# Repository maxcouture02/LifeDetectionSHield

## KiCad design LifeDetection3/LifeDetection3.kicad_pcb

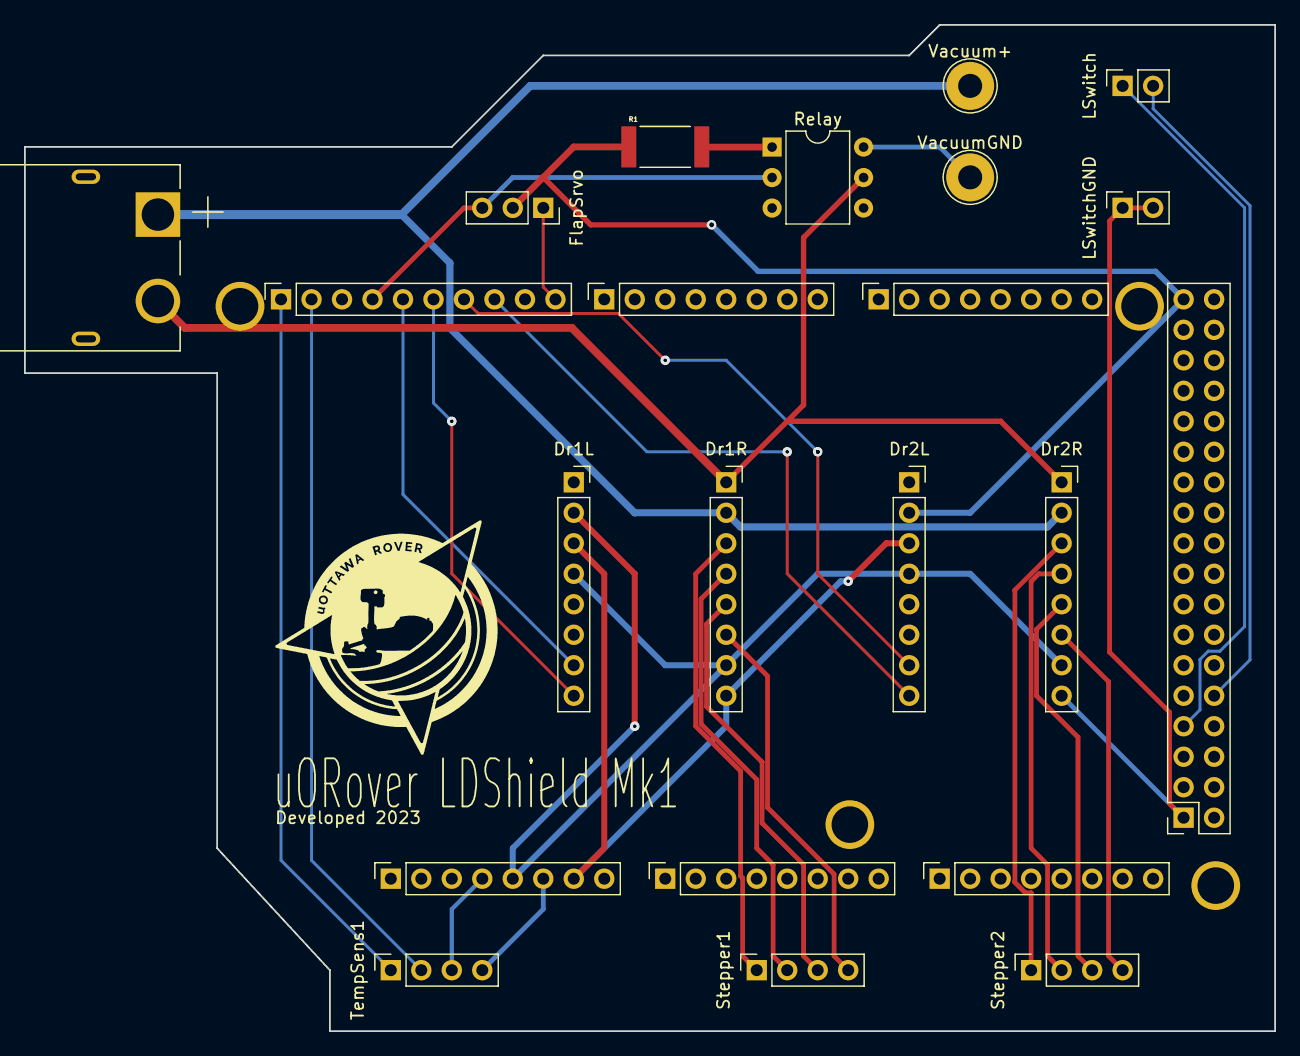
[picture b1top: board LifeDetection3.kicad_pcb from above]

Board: 2 copper layers, 104.1 x 83.8 mm, 22 parts (0 on the bottom side), 24 nets.

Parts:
Dr1L, Dr1R, Dr2L, Dr2R: Conn_01x08; PinSocket_1x08_P2.54mm_Vertical
FlapSrvo: Conn_01x03; PinSocket_1x03_P2.54mm_Vertical
J1: Power; PinSocket_1x08_P2.54mm_Vertical
J2: PWM; PinSocket_1x10_P2.54mm_Vertical
J3, J5: Analog; PinSocket_1x08_P2.54mm_Vertical
J4: PWM; PinSocket_1x08_P2.54mm_Vertical
J6: Communication; PinSocket_1x08_P2.54mm_Vertical
J7: Digital; PinSocket_2x18_P2.54mm_Vertical
J12: XT60PW-M; AMASS_XT60PW-M
LSwitch: Conn_01x02; PinSocket_1x02_P2.54mm_Vertical
LSwitchGND: Conn_01x02; PinSocket_1x02_P2.54mm_Vertical
R1: ERJ-1TNF1240U; RESC6432X70N
Relay: TLP3545; DIP-6_W7.62mm
Stepper1, Stepper2: Conn_01x04; PinSocket_1x04_P2.54mm_Vertical
TempSens1: Conn_01x04; PinSocket_1x04_P2.54mm_Vertical
Vacuum+: Conn_01x01; TestPoint_THTPad_D4.0mm_Drill2.0mm
VacuumGND: Conn_01x01; TestPoint_THTPad_D4.0mm_Drill2.0mm

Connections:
+3V3: J1.4, TempSens1.3
+5V: Dr1L.2, Dr1L.4, Dr1R.7, Dr2L.2, Dr2L.4, Dr2R.7, FlapSrvo.2, J1.5, J7.35, J7.36, R1.1
/47: J7.10, LSwitch.2
/48: J7.7, LSwitch.1
/*8: FlapSrvo.1, J2.10
/*10: Dr2L.8, J2.8
/*11: Dr2L.7, J2.7
/*12: Dr1L.8, J2.6
/*13: Dr1L.7, J2.5
/SCL/21: J2.1, J6.8, TempSens1.1
/SDA/20: J2.2, J6.7, TempSens1.2
GND: Dr1L.3, Dr1R.8, Dr2L.3, Dr2R.8, FlapSrvo.3, J1.6, J1.7, J2.4, J7.1, J7.2, LSwitchGND.1, LSwitchGND.2, Relay.2 (CATHODE), TempSens1.4
unnamed: Dr1R.1, Dr2R.1, J12.2 (-), Relay.5 (SOURCE)
unnamed: Dr1R.2, Dr2R.2, J12.1 (+), Vacuum+.1
unnamed: Dr1R.3, Stepper1.1
unnamed: Dr1R.4, Stepper1.2
unnamed: Dr1R.5, Stepper1.3
unnamed: Dr1R.6, Stepper1.4
unnamed: Dr2R.3, Stepper2.1
unnamed: Dr2R.4, Stepper2.2
unnamed: Dr2R.5, Stepper2.3
unnamed: Dr2R.6, Stepper2.4
unnamed: R1.2, Relay.1 (ANODE)
unnamed: Relay.6 (DRAIN), VacuumGND.1

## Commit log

2023-01-19 Shield
2023-01-20 progress
2023-01-20 lil changes
2023-01-27 2 layers + connector footprint
2023-01-27 logo added
2023-01-27 edge & 3D models
2023-01-27 lil fix
2023-02-02 more tracing
2023-02-02 vias and stuff
2023-02-05 almost done
2023-02-05 final touches
2023-02-07 more final touches
2023-02-07 stuff
